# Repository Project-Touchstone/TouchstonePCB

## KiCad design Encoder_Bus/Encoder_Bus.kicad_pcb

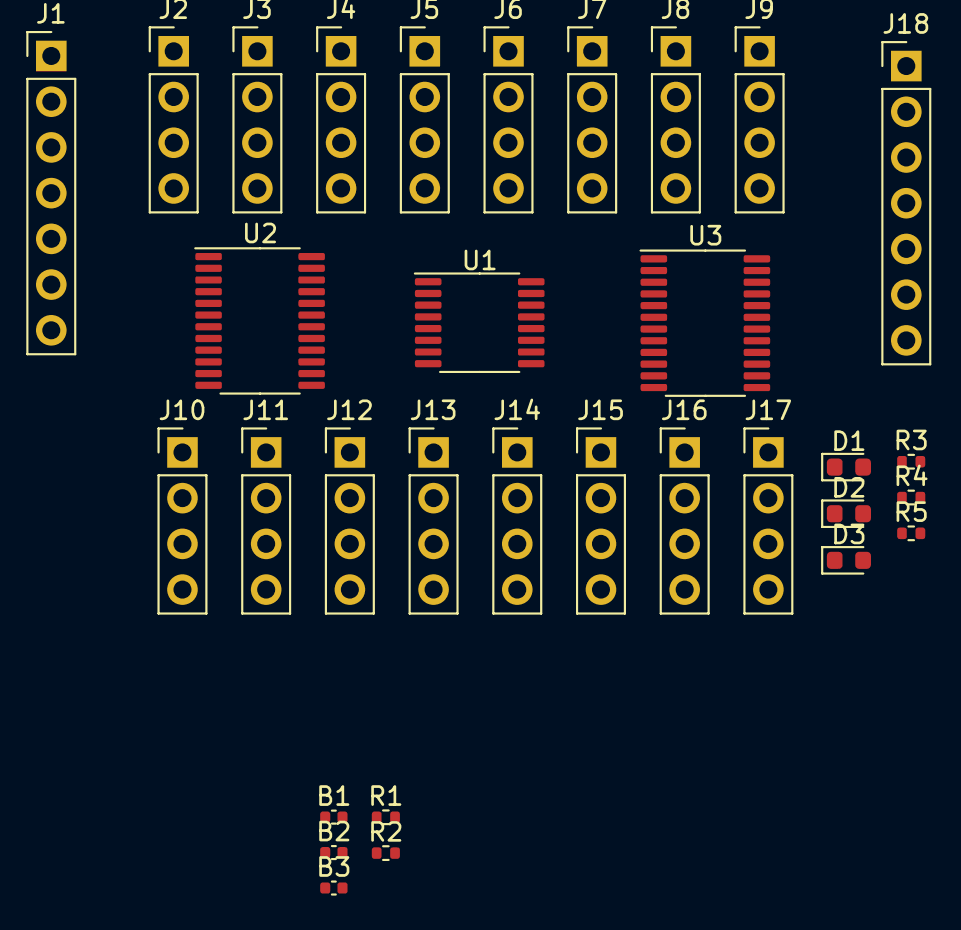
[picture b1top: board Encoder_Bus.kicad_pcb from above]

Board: 2 copper layers, 32 parts (0 on the bottom side), 51 nets, no tracks yet.

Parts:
B1, B2, B3: 0.1u; C_0402_1005Metric
D1, D2, D3: LED; LED_0603_1608Metric
J1, J18: Bonn_01x07; PinHeader_1x07_P2.54mm_Vertical
J2, J3, J4, J5, J6, J7, J8, J9, J10, J11, J12, J13, J14, J15, J16, J17: Bonn_01x04; PinHeader_1x04_P2.54mm_Vertical
R1, R2: 1.2K; R_0402_1005Metric
R3, R4, R5: 500; R_0402_1005Metric
U1: 74HB595; TSSOP-16_4.4x5mm_P0.65mm
U2, U3: TBB9548BPWR; TSSOP-24_4.4x7.8mm_P0.65mm

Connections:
/CLK: J1.3, J18.3, U1.11 (SRCLK)
/ENA: D2.2 (A), U1.7 (QH), U3.3 (~RESET)
/ENB: D3.2 (A), U1.3 (QD), U2.3 (~RESET)
/RCLK: J1.4, J18.4, U1.12 (RCLK)
/SB0A: J2.4, U3.5 (SC0)
/SB0B: J10.4, U2.5 (SC0)
/SB1A: J3.4, U3.7 (SC1)
/SB1B: J11.4, U2.7 (SC1)
/SB2A: J4.4, U3.9 (SC2)
/SB2B: J12.4, U2.9 (SC2)
/SB3A: J5.4, U3.11 (SC3)
/SB3B: J13.4, U2.11 (SC3)
/SB4A: J6.4, U3.14 (SC4)
/SB4B: J14.4, U2.14 (SC4)
/SB5A: J7.4, U3.16 (SC5)
/SB5B: J15.4, U2.16 (SC5)
/SB6A: J8.4, U3.18 (SC6)
/SB6B: J16.4, U2.18 (SC6)
/SB7A: J9.4, U3.20 (SC7)
/SB7B: J17.4, U2.20 (SC7)
/SCL: J1.6, J18.6, R2.1, U2.22 (SCL), U3.22 (SCL)
/SD0A: J2.3, U3.4 (SD0)
/SD0B: J10.3, U2.4 (SD0)
/SD1A: J3.3, U3.6 (SD1)
/SD1B: J11.3, U2.6 (SD1)
/SD2A: J4.3, U3.8 (SD2)
/SD2B: J12.3, U2.8 (SD2)
/SD3A: J5.3, U3.10 (SD3)
/SD3B: J13.3, U2.10 (SD3)
/SD4A: J6.3, U3.13 (SD4)
/SD4B: J14.3, U2.13 (SD4)
/SD5A: J7.3, U3.15 (SD5)
/SD5B: J15.3, U2.15 (SD5)
/SD6A: J8.3, U3.17 (SD6)
/SD6B: J16.3, U2.17 (SD6)
/SD7A: J9.3, U3.19 (SD7)
/SD7B: J17.3, U2.19 (SD7)
/SDA: J1.7, J18.7, R1.1, U2.23 (SDA), U3.23 (SDA)
/SIN: J1.5, U1.14 (SER)
/SOUT: J18.5, U1.9 (QH')
/VCC: B1.2, B2.2, B3.2, D1.2 (A), J1.1, J2.1, J3.1, J4.1, J5.1, J6.1, J7.1, J8.1, J9.1, J10.1, J11.1, J12.1, J13.1, J14.1, J15.1, J16.1, J17.1, J18.1, R1.2, R2.2, U1.10 (~SRCLR), U1.16 (VCC), U2.24 (VCC), U3.24 (VCC)
GND: B1.1, B2.1, B3.1, J1.2, J2.2, J3.2, J4.2, J5.2, J6.2, J7.2, J8.2, J9.2, J10.2, J11.2, J12.2, J13.2, J14.2, J15.2, J16.2, J17.2, J18.2, R3.2, R4.2, R5.2, U1.8 (GND), U1.13 (~OE), U2.12 (GND), U3.12 (GND)
unnamed: D1.1 (K), R3.1
unnamed: D2.1 (K), R4.1
unnamed: D3.1 (K), R5.1
unnamed: U1.15 (QA), U2.21 (A2)
unnamed: U1.1 (QB), U2.2 (A1)
unnamed: U1.2 (QC), U2.1 (A0)
unnamed: U1.4 (QE), U3.21 (A2)
unnamed: U1.5 (QF), U3.2 (A1)
unnamed: U1.6 (QG), U3.1 (A0)

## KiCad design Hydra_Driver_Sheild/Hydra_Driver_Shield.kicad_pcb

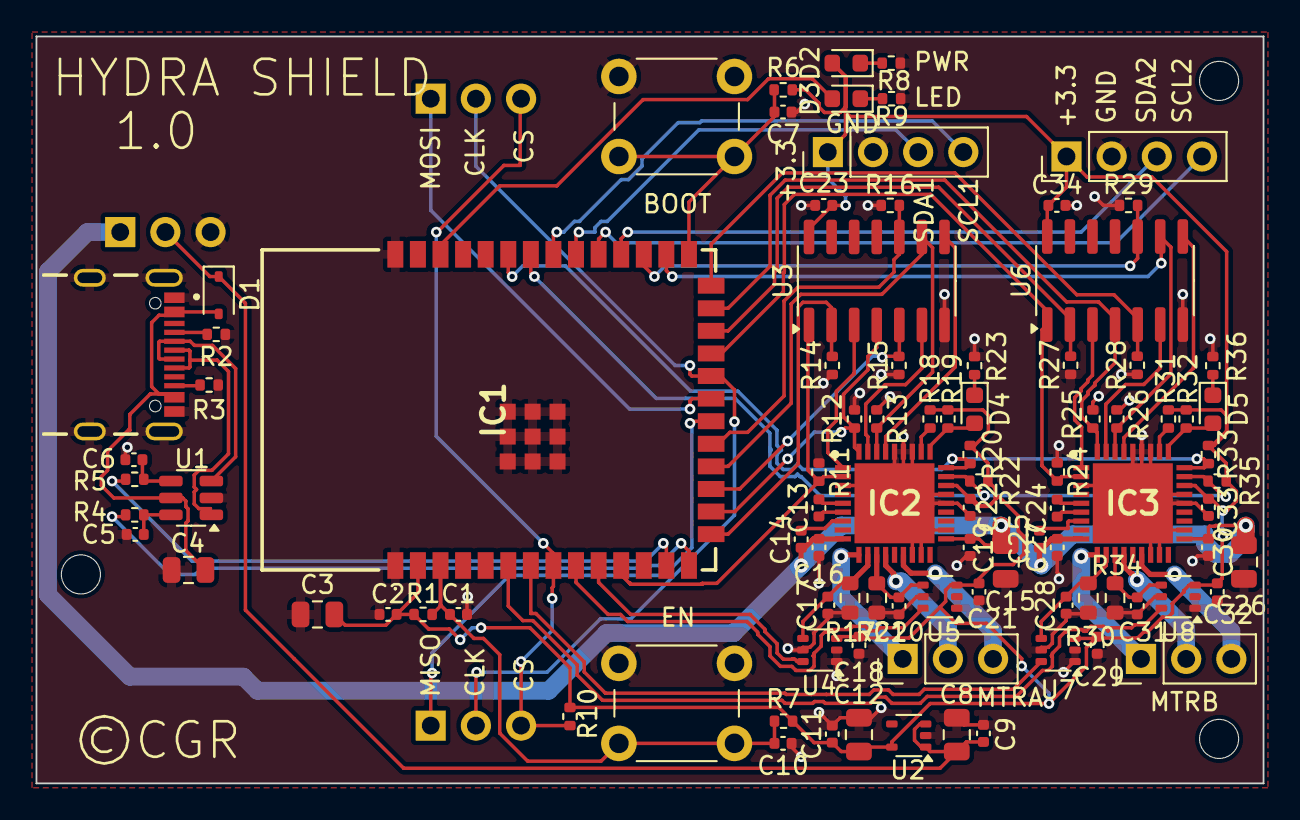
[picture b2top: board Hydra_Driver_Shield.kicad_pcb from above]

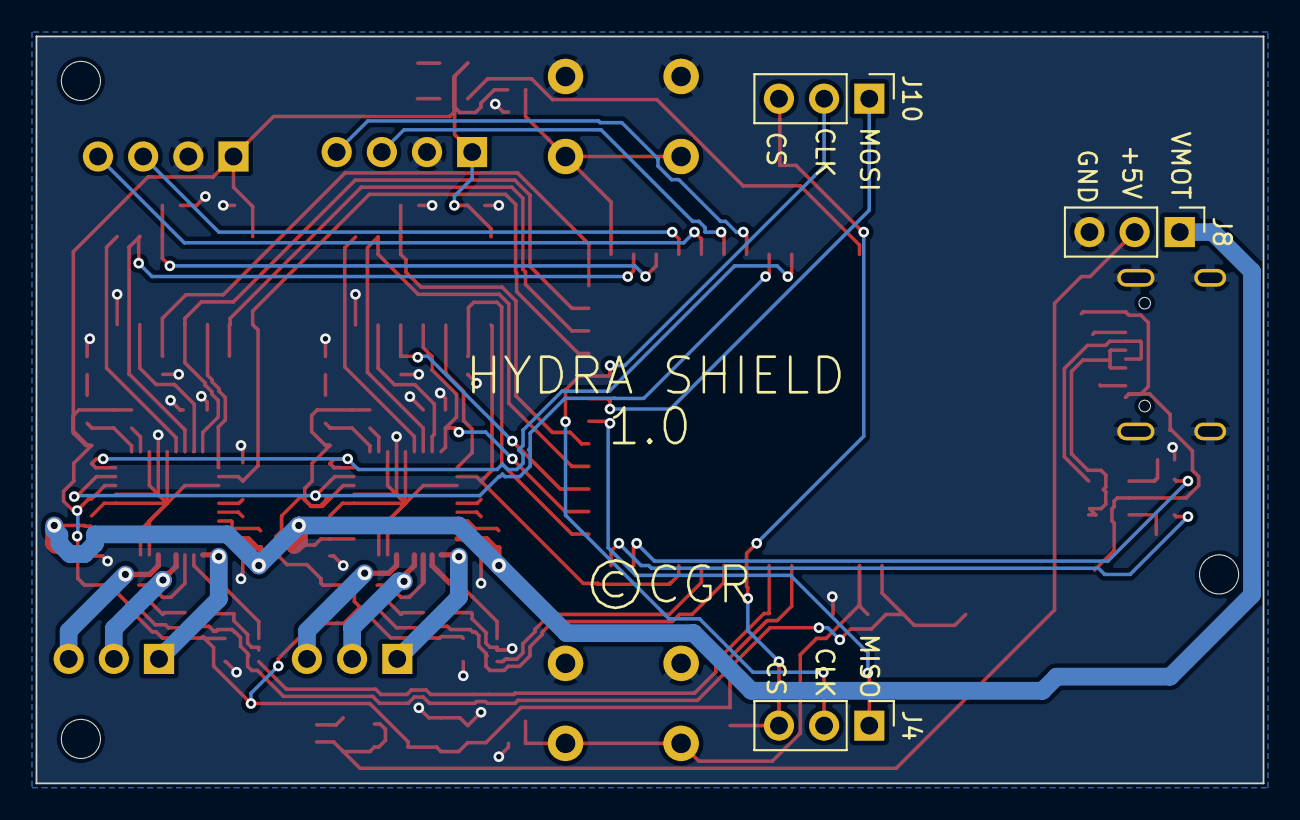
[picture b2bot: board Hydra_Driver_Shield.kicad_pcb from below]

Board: 2 copper layers, 69.0 x 42.0 mm, 96 parts (3 on the bottom side), 72 nets.

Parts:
C1, C2, C7, C9, C10, C11, C14, C16, C17, C18, C19, C20, C21, C23, C25, C27, C28, C29, C30, C31, C32, C34: 0.1u; C_0402_1005Metric
C3, C4, C8, C12, C15, C26: 10u; C_0805_2012Metric
C5, C6: 20p; C_0402_1005Metric
C13, C24: 0.01u; C_0402_1005Metric
C22, C33: 0.47u; C_0402_1005Metric
D1: BAT60A; D_SOD-323
D2, D3, D4, D5: LED; LED_0603_1608Metric
IC1: ESP32-S3-WROOM-1-N4; ESP32S3WROOM1N4
IC2, IC3: DRV8313RHHR; QFN50P600X600X100-37N-D
J1: USB4105-GF-A; GCT_USB4105-GF-A
J4, J6, J8, J10, J12: Conn_01x03; PinHeader_1x03_P2.54mm_Vertical
J5, J11: Conn_01x04; PinHeader_1x04_P2.54mm_Vertical
R1, R6, R7, R10: 10k; R_0402_1005Metric
R2, R3: 5.1kΩ; R_0402_1005Metric
R4, R5: 22Ω; R_0402_1005Metric
R8, R9, R23, R36: 500; R_0402_1005Metric
R11, R12, R13, R14, R15, R16, R18, R19, R20, R22, R24, R25, R26, R27, R28, R29, R31, R32, R33, R35: 3.3k; R_0402_1005Metric
R17, R21, R30, R34: 25m; R_0603_1608Metric
SW1, SW2: SW_SPST; SW_PUSH_6mm
U1: USBLC6-2SC6; SOT-23-6
U2: MIC5365-3.3YC5; SOT-353_SC-70-5
U3, U6: 74HC32; SOIC-14_3.9x8.7mm_P1.27mm
U4, U5, U7, U8: INA199xxDCK; SOT-363_SC-70-6

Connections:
+3.3V: C2.2, C3.2, C11.1, C12.1, C18.2, C21.2, C22.2, C23.1, C29.2, C32.2, C33.2, C34.1, D2.2 (A), IC1.2 (3V3), IC2.25 (V3P3), IC3.25 (V3P3), J5.1, J11.1, R1.1, R6.1, R7.1, R10.2, R18.2, R19.2, R20.2, R22.2, R31.2, R32.2, R33.2, R35.2, U2.5 (VOUT), U3.14 (VCC), U4.3 (V+), U5.3 (V+), U6.14 (VCC), U7.3 (V+), U8.3 (V+)
+5V: C8.1, C9.1, D1.1 (K), J8.2, U2.1 (VIN), U2.3 (EN)
/CHIP_PU: C1.1, C10.1, IC1.3 (EN), R1.2, R7.2, SW2.2 (B)
/CLK: IC1.22 (IO14), J4.2, J10.2
/CS: IC1.8 (IO15), J4.3, J10.3, R10.1
/D+: IC1.14 (IO20), R4.1
/D-: IC1.13 (IO19), R5.1
/Driver_Unit1/EN1: IC3.1 (EN1), U6.3
/Driver_Unit1/EN2: IC3.35 (EN2), U6.6
/Driver_Unit1/EN3: IC3.33 (EN3), U6.8
/Driver_Unit1/FAULT: D5.2 (A), IC3.28 (NFAULT), R32.1
/Driver_Unit1/SGND1: C28.2, IC3.11 (PGND1), R30.1, U7.4 (+)
/Driver_Unit1/SGND2: C31.2, IC3.12 (PGND2), R34.1, U8.4 (+)
/Driver_Unit/EN1: IC2.1 (EN1), U3.3
/Driver_Unit/EN2: IC2.35 (EN2), U3.6
/Driver_Unit/EN3: IC2.33 (EN3), U3.8
/Driver_Unit/FAULT: D4.2 (A), IC2.28 (NFAULT), R19.1
/Driver_Unit/SGND1: C17.2, IC2.11 (PGND1), R17.1, U4.4 (+)
/Driver_Unit/SGND2: C20.2, IC2.12 (PGND2), R21.1, U5.4 (+)
/GPIO0: C7.1, IC1.27 (IO0), R6.2, SW1.2 (B)
/IN1HA: IC1.11 (IO18), IC2.2 (IN1), R11.2, U3.1
/IN1HB: IC1.23 (IO21), IC3.2 (IN1), R24.2, U6.1
/IN1LA: IC1.15 (IO3), R14.2, U3.2
/IN1LB: IC1.24 (IO47), R27.2, U6.2
/IN2HA: IC1.16 (IO46), IC2.36 (IN2), R12.2, U3.4
/IN2HB: IC1.25 (IO48), IC3.36 (IN2), R25.2, U6.4
/IN2LA: IC1.17 (IO9), R15.2, U3.5
/IN2LB: IC1.26 (IO45), R28.2, U6.5
/IN3HA: IC1.18 (IO10), IC2.34 (IN3), R13.2, U3.9
/IN3HB: IC1.28 (IO35), IC3.34 (IN3), R26.2, U6.9
/IN3LA: IC1.19 (IO11), R16.2, U3.10
/IN3LB: IC1.29 (IO36), R29.2, U6.10
/LED: D3.2 (A), IC1.38 (IO2)
/MISO: IC1.20 (IO12), J4.1
/MOSI: IC1.21 (IO13), J10.1
/OUT1A: IC2.10 (OUT1), J6.1
/OUT1B: IC3.10 (OUT1), J12.1
/OUT2A: IC2.13 (OUT2), J6.2
/OUT2B: IC3.13 (OUT2), J12.2
/OUT3A: IC2.15 (OUT3), J6.3
/OUT3B: IC3.15 (OUT3), J12.3
/RESET: IC1.34 (IO41), IC2.26 (NRESET), IC3.26 (NRESET), R22.1, R35.1
/SCL1: IC1.33 (IO40), J11.4
/SCL2: IC1.31 (IO38), J5.4
/SDA1: IC1.32 (IO39), J11.3
/SDA2: IC1.30 (IO37), J5.3
/SENSE1A: IC1.10 (IO17), U4.6
/SENSE1B: IC1.7 (IO7), U7.6
/SENSE2A: IC1.9 (IO16), U5.6
/SENSE2B: IC1.6 (IO6), U8.6
/SLEEP: IC1.35 (IO42), IC2.27 (NSLEEP), IC3.27 (NSLEEP), R20.1, R33.1
GND: C1.2, C2.1, C3.1, C4.1, C5.2, C6.2, C7.2, C8.2, C9.2, C10.2, C11.2, C12.2, C15.1, C16.1, C17.1, C18.1, C19.1, C20.1, C21.1, C22.1, C23.2, C26.1, C27.1, C28.1, C29.1, C30.1, C31.1, C32.1, C33.1, C34.2, IC1.1 (GND_1), IC1.40 (GND_2), IC1.41 (GND_3), IC1.42 (GND_4), IC1.43 (GND_5), IC1.44 (GND_6), IC1.45 (GND_7), IC1.46 (GND_8), IC1.47 (GND_9), IC1.48 (GND_10), IC1.49 (GND_11), IC2.3 (GND_1), IC2.16 (PGND3), IC2.17 (GND_2), IC2.20 (GND_3), IC2.23 (GND_4), IC2.24 (GND_5), IC2.30 (GND_6), IC2.31 (GND_7), IC2.32 (GND_8), IC2.37 (EP), IC3.3 (GND_1), IC3.16 (PGND3), IC3.17 (GND_2), IC3.20 (GND_3), IC3.23 (GND_4), IC3.24 (GND_5), IC3.30 (GND_6), IC3.31 (GND_7), IC3.32 (GND_8), IC3.37 (EP), J1.A1_B12 (GND), J1.B1_A12 (GND__1), J1.SH1 (SHELL_GND), J1.SH2 (SHELL_GND__1), J1.SH3 (SHELL_GND__2), J1.SH4 (SHELL_GND__3), J5.2, J8.3, J11.2, R2.2, R3.2, R8.2, R9.2, R11.1, R12.1, R13.1, R14.1, R15.1, R16.1, R17.2, R21.2, R23.2, R24.1, R25.1, R26.1, R27.1, R28.1, R29.1, R30.2, R34.2, R36.2, SW1.1 (A), SW2.1 (A), U1.2 (GND), U2.2 (GND), U3.7 (GND), U4.1 (REF), U4.2 (GND), U4.5 (-), U5.1 (REF), U5.2 (GND), U5.5 (-), U6.7 (GND), U7.1 (REF), U7.2 (GND), U7.5 (-), U8.1 (REF), U8.2 (GND), U8.5 (-)
unnamed: C5.1, R4.2, U1.6 (I/O1)
unnamed: C6.1, R5.2, U1.4 (I/O2)
unnamed: C4.2, D1.2 (A), J1.A4_B9 (VBUS), J1.B4_A9 (VBUS__1), U1.5 (VBUS)
unnamed: D2.1 (K), R8.1
unnamed: D3.1 (K), R9.1
unnamed: D4.1 (K), R23.1
unnamed: D5.1 (K), R36.1
unnamed: C13.1, IC2.6 (CPH)
unnamed: C13.2, IC2.5 (CPL)
unnamed: IC2.29 (NCOMPO), R18.1
unnamed: C14.2, IC2.7 (VCP)
unnamed: C24.1, IC3.6 (CPH)
unnamed: C24.2, IC3.5 (CPL)
unnamed: IC3.29 (NCOMPO), R31.1
unnamed: C25.2, IC3.7 (VCP)
unnamed: J1.A5 (CC1), R2.1
unnamed: J1.B5 (CC2), R3.1
unnamed: J1.A7 (DN1), J1.B7 (DN2), U1.3 (I/O2)
unnamed: J1.A6 (DP1), J1.B6 (DP2), U1.1 (I/O1)
VMOT: C14.1, C15.2, C16.2, C19.2, C25.1, C26.2, C27.2, C30.2, IC2.9 (VM_1), IC2.19 (VM_2), IC3.9 (VM_1), IC3.19 (VM_2), J8.1

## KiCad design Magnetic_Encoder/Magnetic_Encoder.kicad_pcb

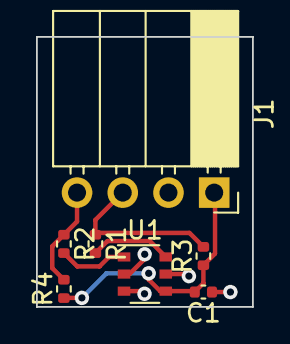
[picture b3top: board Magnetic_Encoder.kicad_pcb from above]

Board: 2 copper layers, 12.0 x 15.0 mm, 7 parts (0 on the bottom side), 6 nets.

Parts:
C1: 0.1uF; C_0402_1005Metric
J1: Conn_01x04; PinSocket_1x04_P2.54mm_Horizontal
R1, R2: 100; R_0402_1005Metric
R3, R4: 1.2K; R_0402_1005Metric
U1: TLV493D-A1B6; TSOP-6_1.65x3.05mm_P0.95mm

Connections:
/SCL: J1.4, R2.1, R4.2
/SDA: J1.3, R1.1, R3.2
/VCC: C1.2, J1.1, R3.1, R4.1, U1.4 (VCC)
GND: C1.1, J1.2, U1.2 (GND), U1.3 (GND), U1.5 (GND)
unnamed: R2.2, U1.1 (SCL)
unnamed: R1.2, U1.6 (SDA)

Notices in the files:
Hydra_Driver_Sheild/Hydra_Driver_Shield.kicad_pcb:
©CGR
